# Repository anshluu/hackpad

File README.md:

# Anshul's hackpad

This is my hackpad! It has 8 backlit keys, a dial, an OLED, and a status LED.

# Schematic 

# PCB

# Case!

# BOM
| Part    | Quantity |
| -------- | ------- |
| SK6812MINI LED  | 9    |
| Rotary Encoder | 1     |
| Cherry MX Switch  | 8    |
| Diodes  | 9   |
| OLED  | 1   |
| XIAO-RP2040  | 1    |

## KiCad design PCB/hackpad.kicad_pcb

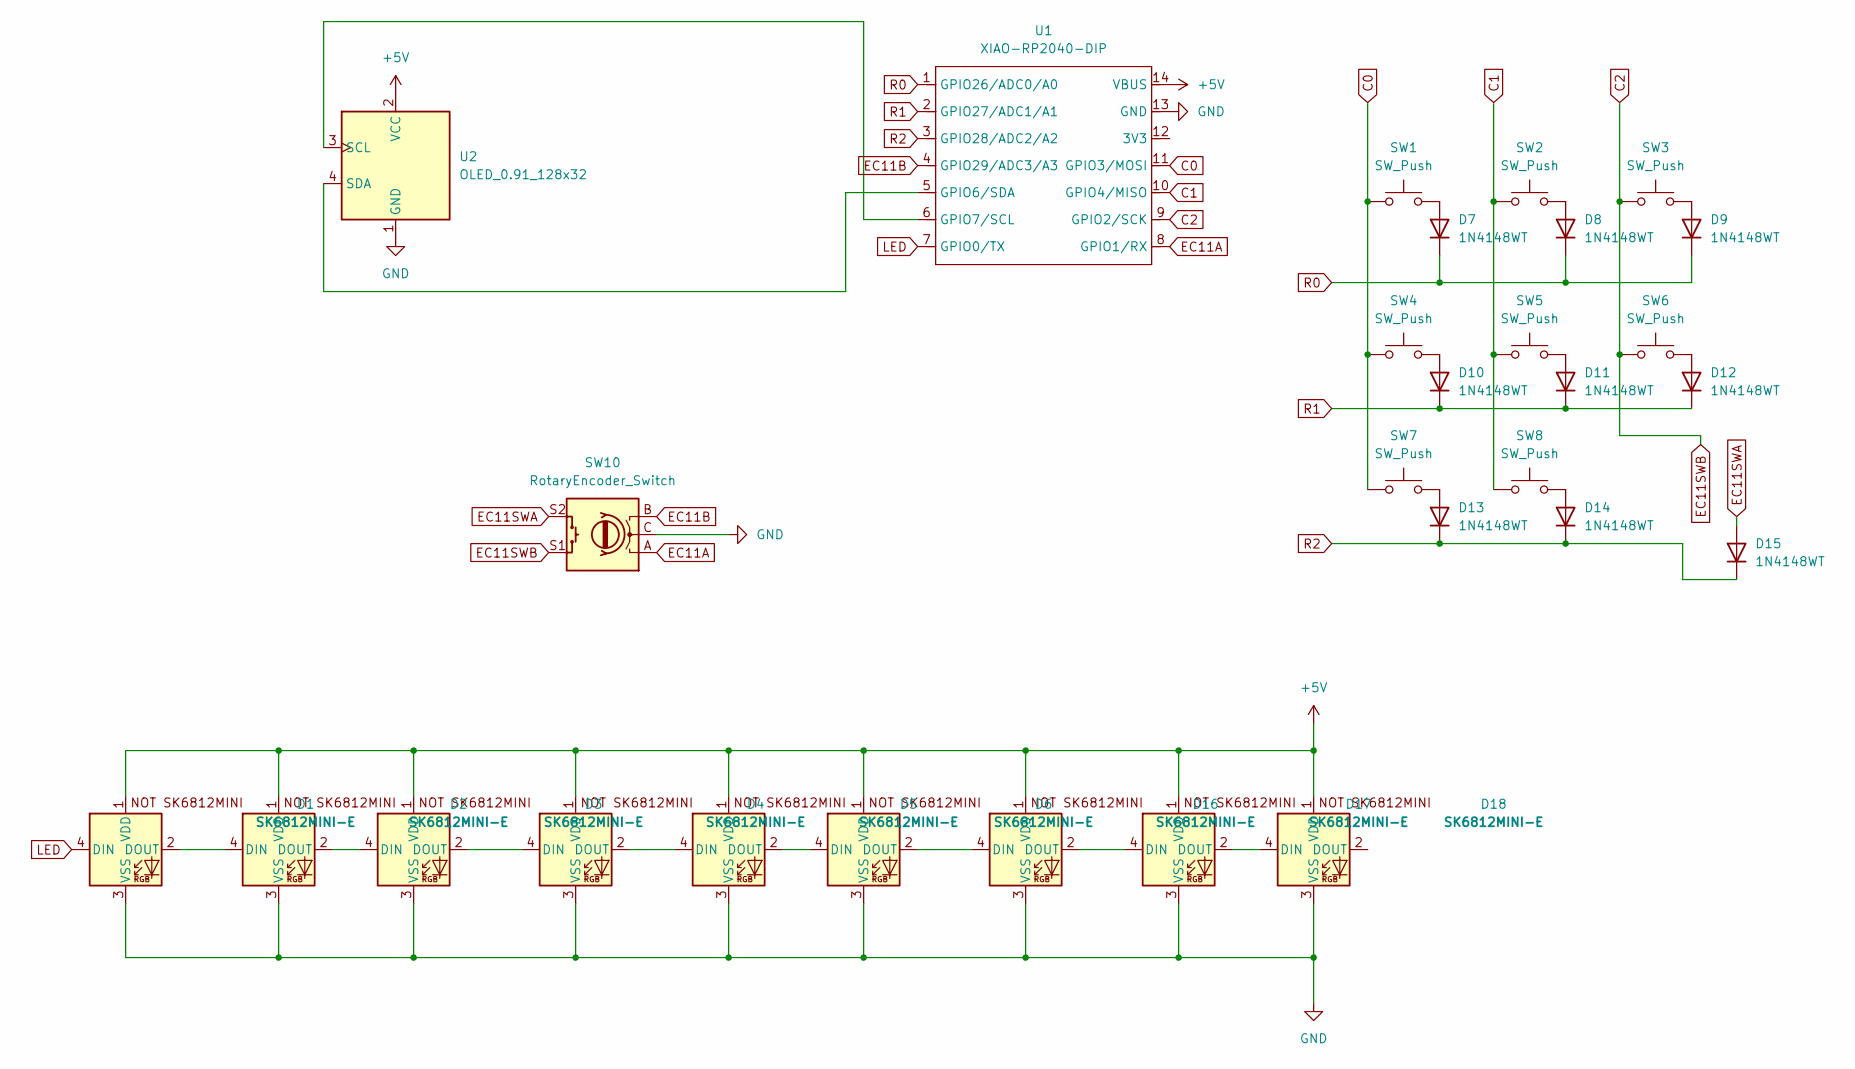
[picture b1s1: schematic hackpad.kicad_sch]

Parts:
D1, D2, D3, D4, D5, D6, D16, D17, D18: SK6812MINI-E; SK6812MINI-E_fixed
D7, D8, D9, D10, D11, D12, D13, D14, D15: 1N4148WT; D_DO-35_SOD27_P7.62mm_Horizontal
SW1, SW2, SW3, SW4, SW5, SW6, SW7, SW8: SW_Push; SW_Cherry_MX_1.00u_PCB
SW10: RotaryEncoder_Switch; RotaryEncoder_Alps_EC11E-Switch_Vertical_H20mm
U1: XIAO-RP2040-DIP
U2: OLED_0.91_128x32

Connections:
+5V: D1.1 (VDD), D2.1 (VDD), D3.1 (VDD), D4.1 (VDD), D5.1 (VDD), D6.1 (VDD), D16.1 (VDD), D17.1 (VDD), D18.1 (VDD), U1.14 (VBUS), U2.2 (VCC)
C0: SW1.1, SW4.1, SW7.1, U1.11 (GPIO3/MOSI)
C1: SW2.1, SW5.1, SW8.1, U1.10 (GPIO4/MISO)
C2: SW3.1, SW6.1, SW10.S1, U1.9 (GPIO2/SCK)
EC11A: SW10.A, U1.8 (GPIO1/RX)
EC11B: SW10.B, U1.4 (GPIO29/ADC3/A3)
EC11SWA: D15.2 (A), SW10.S2
GND: D1.3 (VSS), D2.3 (VSS), D3.3 (VSS), D4.3 (VSS), D5.3 (VSS), D6.3 (VSS), D16.3 (VSS), D17.3 (VSS), D18.3 (VSS), SW10.C, U1.13 (GND), U2.1 (GND)
LED: D1.4 (DIN), U1.7 (GPIO0/TX)
unnamed: D1.2 (DOUT), D2.4 (DIN)
unnamed: D2.2 (DOUT), D3.4 (DIN)
unnamed: D3.2 (DOUT), D4.4 (DIN)
unnamed: D4.2 (DOUT), D5.4 (DIN)
unnamed: D5.2 (DOUT), D6.4 (DIN)
unnamed: D7.2 (A), SW1.2
unnamed: D8.2 (A), SW2.2
unnamed: D9.2 (A), SW3.2
unnamed: D10.2 (A), SW4.2
unnamed: D11.2 (A), SW5.2
unnamed: D12.2 (A), SW6.2
unnamed: D13.2 (A), SW7.2
unnamed: D14.2 (A), SW8.2
unnamed: D6.2 (DOUT), D16.4 (DIN)
unnamed: D16.2 (DOUT), D17.4 (DIN)
unnamed: D17.2 (DOUT), D18.4 (DIN)
unnamed: U1.5 (GPIO6/SDA), U2.4 (SDA)
unnamed: U1.6 (GPIO7/SCL), U2.3 (SCL)
R0: D7.1 (K), D8.1 (K), D9.1 (K), U1.1 (GPIO26/ADC0/A0)
R1: D10.1 (K), D11.1 (K), D12.1 (K), U1.2 (GPIO27/ADC1/A1)
R2: D13.1 (K), D14.1 (K), D15.1 (K), U1.3 (GPIO28/ADC2/A2)

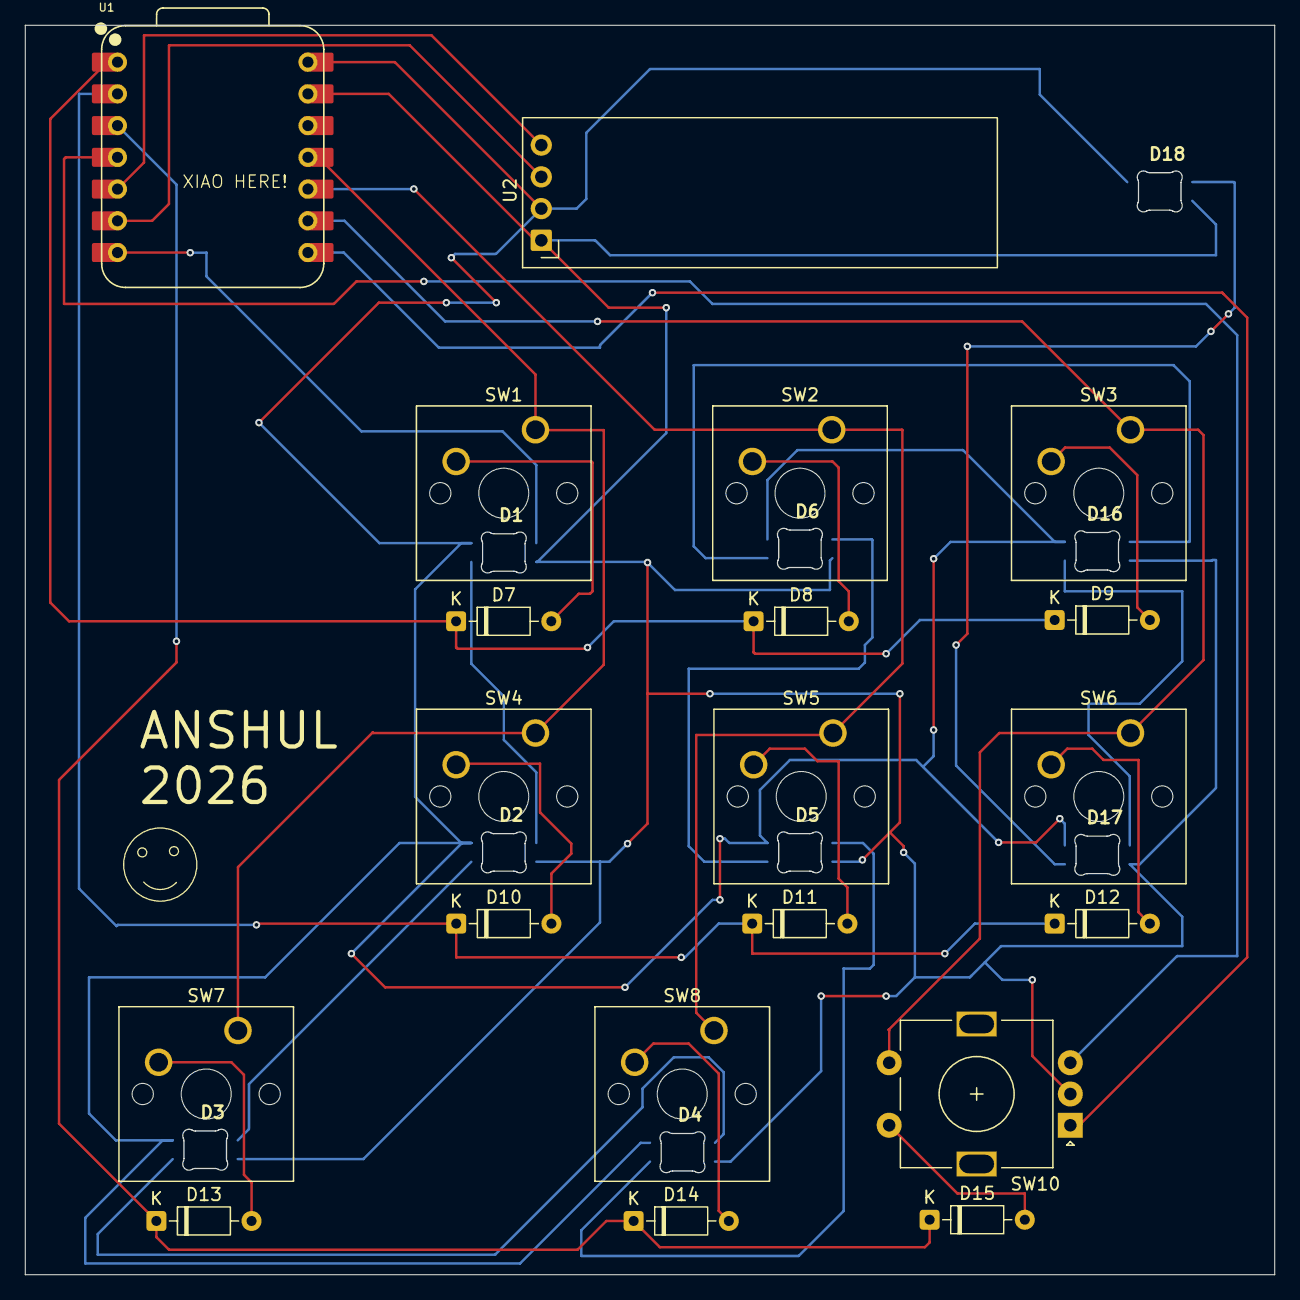
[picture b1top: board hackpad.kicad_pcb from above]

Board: 2 copper layers, 100.0 x 100.0 mm, 29 parts (0 on the bottom side), 30 nets.

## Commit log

2026-02-08 added files
2026-02-08 Enhance README with images and BOM details
    Added images and descriptions for schematic, PCB, case, and BOM.
2026-02-08 Rename RotaryKnob.step to CaseKnob.step
2026-02-08 case knob
